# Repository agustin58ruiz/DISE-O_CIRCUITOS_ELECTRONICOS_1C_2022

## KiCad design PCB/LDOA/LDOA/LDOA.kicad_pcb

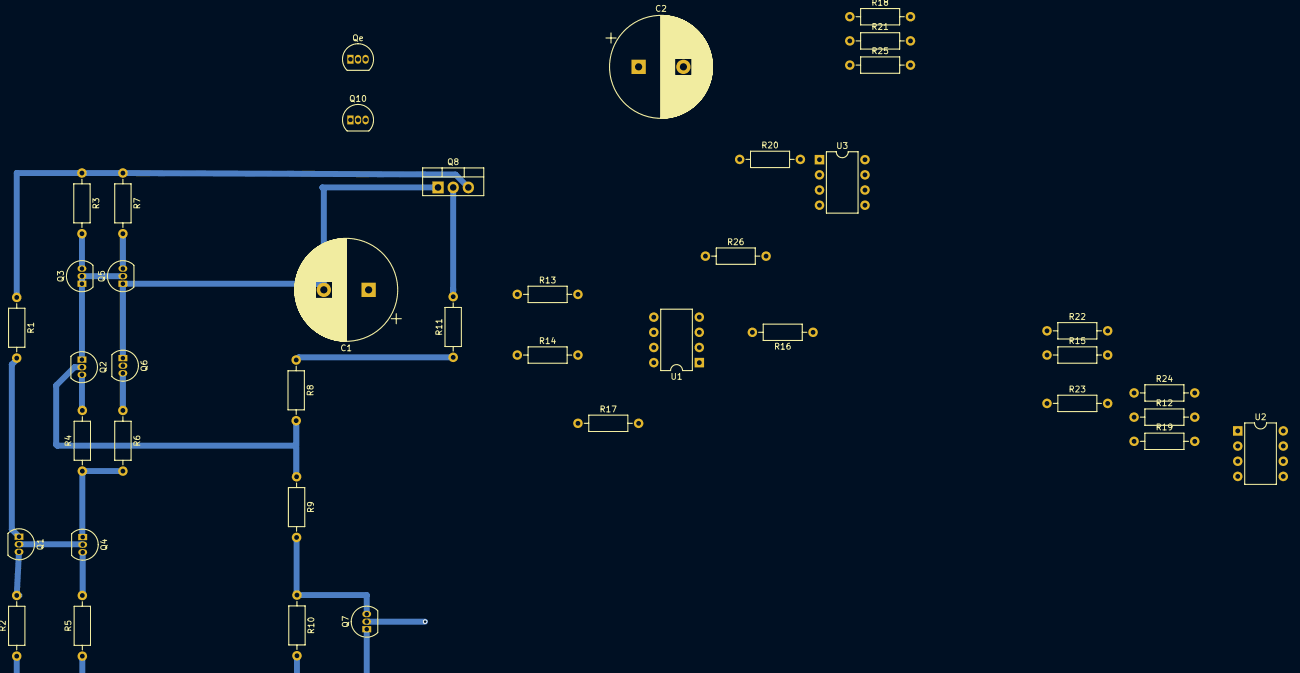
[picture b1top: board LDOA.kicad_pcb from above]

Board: 2 copper layers, 41 parts (0 on the bottom side), 29 nets.

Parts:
C1, C2: C; CP_Radial_D17.0mm_P7.50mm
Q1, Q2, Q4, Q6: BC547; TO-92_Inline
Q3, Q5: BC557; TO-92_Inline
Q7: 2N7000; TO-92_Inline
Q8: IRF9520; TO-220-3_Vertical
Q10: BS250; TO-92_Inline
Qe: BS250; TO-92_Inline
R1, R2, R3, R4, R5, R6, R7, R8, R9, R10, R11, R12, R13, R14, R15, R16, R17, R18, R19, R20, R21, R22, R23, R24, R25, R26: R; R_Axial_DIN0207_L6.3mm_D2.5mm_P10.16mm_Horizontal
U1, U2, U3: TL081; DIP-8_W7.62mm

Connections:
/V-: U1.4, U2.4, U3.4
/Vact: C2.1, Q10.2, R26.2, U3.6
/Vref2: R21.2, R23.1, U2.6
/Vsens: R17.2, R22.1, U1.6
GND: Q7.1, R2.1, R5.1, R10.2, R15.2, R16.1, R18.1, R24.2
unnamed: C1.1, Q8.2, R11.2, R13.1
unnamed: C1.2, Q5.1, Q6.1, Q8.1, Q10.1, Qe.1
unnamed: C2.2, R25.2
unnamed: Q1.1, Q1.2, Q4.2, R1.2
unnamed: Q1.3, R2.2
unnamed: Q2.1, Q3.1, Q3.2, Q5.2
unnamed: Q2.3, R4.2
unnamed: Q3.3, R3.2
unnamed: Q4.1, R4.1, R6.2
unnamed: Q4.3, R5.2
unnamed: Q5.3, R7.2
unnamed: Q6.3, R6.1
unnamed: Q7.3, R9.2, R10.1
unnamed: R12.1, R15.1, R19.1
unnamed: R13.2, R16.2, U1.3
unnamed: R14.2, R17.1, U1.2
unnamed: R18.2, R21.1, U2.2
unnamed: R19.2, R20.2, U2.3
unnamed: R22.2, R25.1, R26.1, U3.2
unnamed: R23.2, R24.1, U3.3
VA: R8.1, R11.1, R14.1
VREG: Q8.3, Q10.3, Qe.3, R1.1, R3.1, R7.1, U1.7, U2.7, U3.7
Vf: Q2.2, R8.2, R9.1, R20.1
Vref: Q6.2, R12.2

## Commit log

2022-04-08 Nuevo esquematico: LDO en bloques para testear PMOS como transistor de paso
2022-04-09 Diagrama en bloques cambios en clase
2022-04-11 Cambios 11-04
2022-04-13 Ordeno el esqumatico, agrego PMOS como switch en el realimentador
2022-04-17 Amplificador de error con sumidero de corriente (baja 5 veces ICQ y la ganancia se mantiene igual)
2022-04-17 gitignore
2022-04-17 Limpieza
2022-04-17 Update .gitignore
    Diagrama_en_bloques_regulador_sumidero.raw
    Diagrama_en_bloques_regulador_sumidero.log
2022-04-18 Agrego archivo con modelo de irf9520
2022-04-21 Versión con transistor de salida real y foldback
2022-04-21 sumidero de corriente
2022-04-22 gitignore update
2022-04-22 agrego pmos real como transistor de paso, simulaciones funcionan barbaro
2022-04-22 Cambio de lugar la R con switch del bloque realim en base a los comentarios del profe
2022-04-22 Elimino .log - Limpieza
    Limpiando archivos
2022-04-22 Elimino .raw - Limpieza
2022-04-22 Elimino .log - Limpieza
2022-04-22 Elimino un asc que quedo re viejo
    Era el primer LDO que planteamos con transistor de paso darlington sin mucho mas que el par diferencial
2022-04-22 Renombro archivo
2022-04-22 Elimino asc que quedo viejo - LDO con Pmos real pero sin sumidero ni foldback
2022-04-22 Correccion del bloque realim para dejar R7 invariable por el swtich
2022-04-30 Agrego foldback implementado en bloques
2022-04-30 Prueba de Foldback I
2022-04-30 Sensado de corriente para el Foldback (f=1)
2022-04-30 sensado de corriente para el foldback f=1
2022-05-02 Foldback implementado
2022-05-02 Agregué el amplificador de error del foldback
2022-05-04 fixing broken dependecies
2022-05-11 Compensados los dos lazos.
2022-05-16 Se agrego el archivo OVLO UVLO
    En el archivo hay una implementación del circuito OVLO/UVLO.
2022-05-16 Hoja de calculo para OVLO UVLO
2022-05-18 Resistencias de valores reales y actualización al circuito.
2022-05-20 Agrego Vf al lazo de corriente y los tb para medir el pmos del Buck
2022-05-21 Agrego archivo para hacer los cálculos del transistor de buck
2022-05-23 Limpié archivos y dejé el diseño final del LDOB.
2022-05-23 Edité el símbolo del LDOB
2022-05-23 Subo archivo de modelo TL081 y símbolo
2022-05-23 Subo versión de buck que no funciona bien y el archivo de cálculos corregido.
2022-05-23 Corregí foldback
2022-05-23 Elegimos transistor para el buck
2022-05-24 creo simbolo LDOA, ajusto detalles LDOB y quedan completos ambos menos UVLOOVLO
2022-05-24 verificacion LDO
2022-05-24 Arreglamos correcciones del profesor en el buck
2022-05-26 Se agrego el OVLO UVLO en el archivo LDOA_with_OVLO*
2022-05-28 cambios en el archivo de calculos para OVLO UVLO
2022-05-28 Limpieza del esquematico. Reorganizacion.
2022-05-28 Limpieza de archivo. Reorganizacion
2022-05-28 UVLO agregado y funcionando
2022-05-28 Reorganizacion del circuito, separacion en bloques
2022-05-29 Agrego bloque OVLO pero solo sensa, no actua
2022-05-30 Agregados archivos de Monte Carlo
2022-05-30 LDOB montecarlo actualizado
2022-05-30 Buck ideal arreglado
2022-05-30 Agrego mediciones para LDOB_mc
2022-05-30 Mediciones mc
2022-05-30 Ajustes mediciones mc
2022-05-30 agrego fuente partida
2022-05-30 Excel para volcar mediciones y graficar
2022-05-31 Mediciones MC LDOB realizadas
2022-05-31 LDOA_mc listo para medir mc
2022-06-01 Mediciones LDOB_mc volcadas con histogramas, desvio estandar y promedio. Lo mismo con casi todas las mediciones del LDOA_mc. Faltan mediciones OVLO 5V porque resulta dificil simular las condiciones. 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
2022-06-02 Agregado modelos reales de MOSFETs
2022-06-03 Mediciones UVLO MC
2022-06-03 Mediciones OVLO
2022-06-03 R de sangrado - OVLO
2022-06-04 Ajuste resistencia histeresis OVLO
2022-06-05 WC UVLO/OVLO
2022-06-05 Ovlo Uvlo WC
2022-06-06 Mediciones UVLO OVLO terminadas
2022-06-06 Actualizo unos ajustes al OVLO en el resto de los archivos
2022-06-07 Agregué devuelta el NOT
2022-06-10 Mediciones wc y mc LDOs terminadas
2022-06-10 Calculos del DISIPADOR
2022-06-11 Ajusto valores UVLO y OVLO en base a los comentarios del profe. Aumento la referencia
2022-06-11 Midiendo los 3.3V WC de vuelta para chequear resultados
2022-06-11 Agrego comparador, compara Verr y Vsaw. Funcionando
2022-06-11 agregado del circuito para generar diente de sierra
2022-06-12 Ajusté para Vref 1.2V
2022-06-13 Se acomodaron componentes en el PCB del circuito LDOA, También se agregó el foldback. Todavía falta sumar el UVLO OVLO, y poner los bornes para entradas y salidas del circuito.
2022-06-13 Se agregaron más componentes al PCB. Hay que seguir trabajando con la distrubicion de los componentes
2022-06-14 ajuste del diente de sierra
2022-06-14 Agrego análisis AC de buck
2022-06-15 Agregué dead timer y compensé el lazo
2022-06-16 Se agregaron mas pistas. Hay que avanzar con la inclusion del UVLO OVLO, terminales y demás
2022-06-24 agregue script para ver datos simulados en matlab
2022-06-24 subo resultados
2022-06-25 adapté archivos para tomar modelos desde la carpeta del proyecto
2022-06-26 Agrego modulo de buck. Se arreglan las oscilaciones
2022-06-27 Agregue snub y control de dv/dt
2022-06-27 OVLO UVLO
2022-06-27 agrego compuertas y archivo para simular dead time
2022-06-28 acortamos el delay generado por el circuito de dead time
2022-06-28 agregué soft start y arreglé la compensación
2022-06-29 Agregado UVLO, OVLO (sensando nomas) y OCP (sensando nomas) con latch
2022-06-29 OVLO y OCP Actuan apagando el buck
2022-06-29 ajusté ovlo para actuar en 8v
2022-07-01 Se agregaron los cálculos para el inductor capacitor
2022-07-02 simulaciones hechas en buck
2022-07-03 Function computeKg done. Improvements in inductor computation
2022-07-03 Functions added to inductor
2022-07-04 Program for calculate inductor finished. Set variaples properly in order to use it.
2022-07-06 Leve ajuste estetico para screnshots
2022-07-06 Reg carga din
2022-07-09 Mediciones
2022-07-15 creación de tb
2022-07-15 agrego carpeta para entregar
2022-07-15 Agrego archivos del LDO a la carpeta para entregar
2022-07-15 imagenes de las partes del circuito
2022-09-02 LDOB
2025-01-02 Creo archivo para el bloque support
